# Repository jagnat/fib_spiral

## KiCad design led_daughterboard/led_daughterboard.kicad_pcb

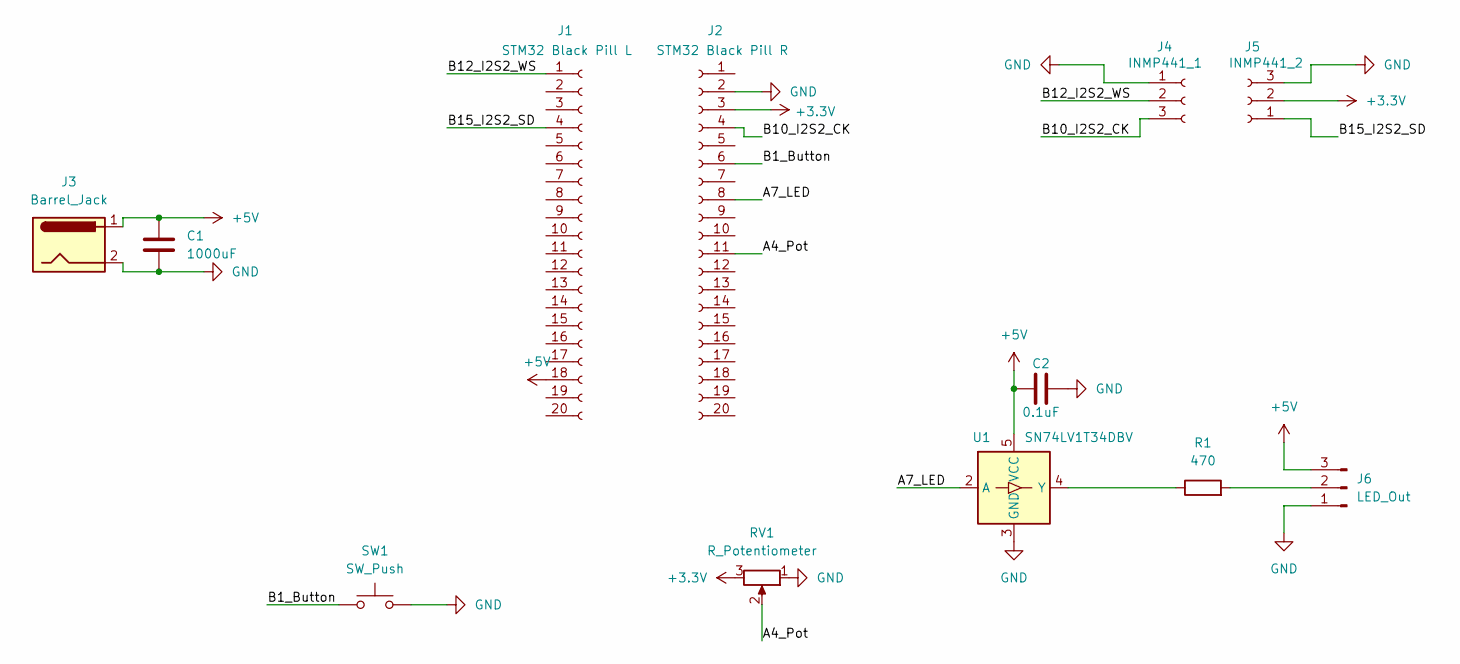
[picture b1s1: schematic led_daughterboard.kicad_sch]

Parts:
C1: 1000uF; CP_Radial_D8.0mm_P3.80mm
C2: 0.1uF; C_0603_1608Metric_Pad1.08x0.95mm_HandSolder
J1: STM32 Black Pill L; PinSocket_1x20_P2.54mm_Vertical
J2: STM32 Black Pill R; PinSocket_1x20_P2.54mm_Vertical
J3: Barrel_Jack; BarrelJack_Horizontal
J4: INMP441_1; PinSocket_1x03_P2.54mm_Vertical
J5: INMP441_2; PinSocket_1x03_P2.54mm_Vertical
J6: LED_Out; JST_XA_S03B-XASK-1_1x03_P2.50mm_Horizontal
R1: 470; R_Axial_DIN0207_L6.3mm_D2.5mm_P10.16mm_Horizontal
RV1: R_Potentiometer; Potentiometer_Alps_RK09K_Single_Vertical
SW1: SW_Push; SW_Push_1P1T_NO_E-Switch_TL3301NxxxxxG
U1: SN74LV1T34DBV; SOT-23-5_HandSoldering

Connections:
+3.3V: J2.3, J5.2, RV1.3
+5V: C1.1, C2.1, J1.18, J3.1, J6.3, U1.5 (VCC)
/A4_Pot: J2.11, RV1.2
/A7_LED: J2.8, U1.2 (A)
/B1_Button: J2.6, SW1.1
/B10_I2S2_CK: J2.4, J4.3
/B12_I2S2_WS: J1.1, J4.2
/B15_I2S2_SD: J1.4, J5.1
GND: C1.2, C2.2, J2.2, J3.2, J4.1, J5.3, J6.1, RV1.1, SW1.2, U1.3 (GND)
unnamed: J6.2, R1.2
unnamed: R1.1, U1.4 (Y)

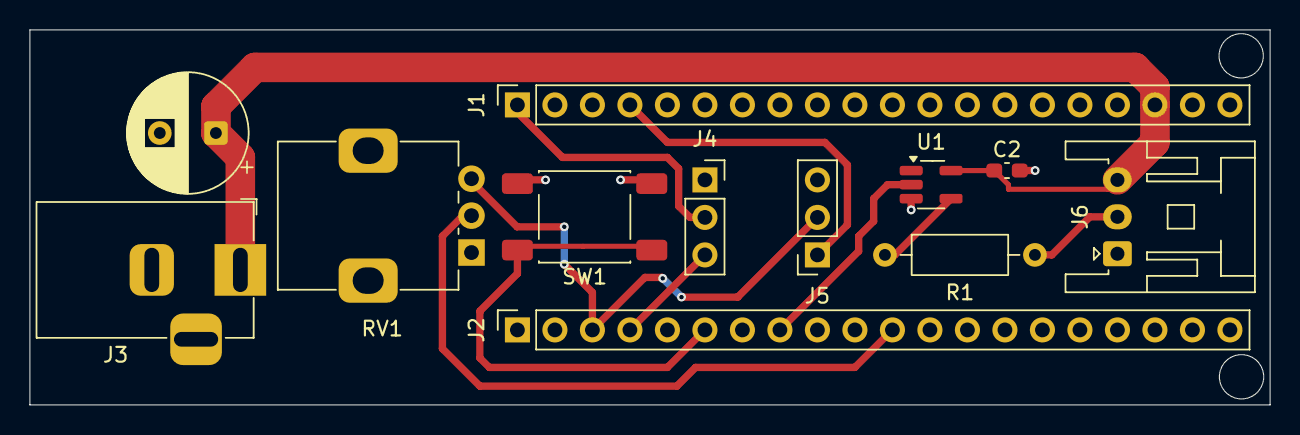
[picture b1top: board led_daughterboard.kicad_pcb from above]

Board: 2 copper layers, 84.0 x 25.4 mm, 12 parts (0 on the bottom side), 11 nets.

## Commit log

2025-12-05 Initial commit (not very initial but w/e)
2025-12-06 Add led ordering reference
2025-12-18 Change order, more 3d printed model stuff
2026-01-05 Add generator for floating point position C LUT
2026-01-06 Add KiCad daughterboard files
2026-01-06 Some tweaks to render colors to the spiral
2026-01-06 Start the messy tracing
2026-01-09 daughterboard tweaks
